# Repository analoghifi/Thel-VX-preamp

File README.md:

### "VX-D" (2007 - 2016):  
* fully discrete circuit (all transistors / no OP-Amps)
* single ended input
* single ended output
* AC coupled input (with film/foil input cap)
* MOSFET Class-A output
* very low-impedance output / is able to drive 1W @ 8Ω (8Ω short-term / 22Ω permanently)
* adjustable gain (16 steps)
* can also be used very well as a "high-end" headphone amplifier
* operating voltage min./max.: ±9V .. ±63V (optimum: ±24V .. ±36V)
  
https://web.archive.org/web/20070809231533/http://www.thel-audioworld.de/module/VXD/vxd.htm  
https://web.archive.org/web/20160325140821/http://thel-audioworld.de/module/VXD/vxd.htm  
<hr>  

### "VX-Line" (from 03/2017):  
* OP-Amp input stage (LME 49720)
* balanced input
* single ended output
* DC coupled
* MOSFET Class-A output (itegrated into the OP-Amps feedback loop)
* very low-impedance output / is able to drive 1W @ 8Ω (8Ω short-term / 22Ω permanently)
* adjustable gain (5 steps)
* can also be used very well as a "high-end" headphone amplifier
* operating voltage min./max.: ±9V .. ±35V (optimum: ±18V .. ±24V)
  
https://web.archive.org/web/20170523101631/http://www.thel-audioworld.de/module/VX-Line/vx-line.htm  
https://web.archive.org/web/20210514101836/http://thel-audioworld.de/module/VX-Line/vx-line.htm  
  
2 different generations of PCB:  
* 2017 - 2020
* from 2021
  
----  
### Kicad projects in this repo:  
* [VX-Line_2021__original](https://github.com/analoghifi/Thel-VX-preamp/tree/main/VX-Line/hardware/KiCad/VX-Line_2021__original) | state: initial release v1.01 | like the original, 1-layer, THT
* [VX-D_original](https://github.com/analoghifi/Thel-VX-preamp/tree/main/VX-D/hardware/KiCad/VX-D_original) | state: coming soon... | like the original, 1-layer, THT

----

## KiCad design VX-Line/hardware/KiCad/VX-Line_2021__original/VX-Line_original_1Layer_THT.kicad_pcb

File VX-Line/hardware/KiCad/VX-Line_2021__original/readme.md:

this is not the original Thel PCB but it's very like\* the original with the following exceptions:  
* more massive ground and power supply PCB tracks  
* using a combined 2.5mm/5.0mm pin spacing footprint for the small ceramic caps (C1,C2,C3,C11)  
  
\*(same schematic / same board dimensions / same 1-layer\** layout THT / same THT components in the same places on the board)  
\**(strictly speaking, this KiCad PCB is a two-layer PCB with plated-through holes, but you can also (let) produce it as a classic 1-layer PCB with non-plated holes if you wish, since all the tracks are on the bottom side only)  

----  

### remarks:  
#### U1:  
instead of [LME49720](https://www2.mouser.com/ProductDetail/Texas-Instruments/LME49720NA-NOPB?qs=7lkVKPoqpbYtIqwyg5iDaA%3D%3D) you can use [LM4562](https://www2.mouser.com/ProductDetail/Texas-Instruments/LM4562NA-NOPB?qs=QbsRYf82W3Gc2w4DLq%252BZjw%3D%3D) (both Texas Instruments),  
these two are 100% identical (even regarding their inner guts).
  
----  

these are KiCad 6.x projects  
see how to get the proper 3D-Models from here: https://github.com/analoghifi/KiCad-3D-Models  

use kicanvas.org to see this KiCad-Project in your browser:  
https://kicanvas.org/?github=https%3A%2F%2Fgithub.com%2Fanaloghifi%2FThel-VX-preamp%2Ftree%2Fmain%2FVX-Line%2Fhardware%2FKiCad%2FVX-Line_2021__original

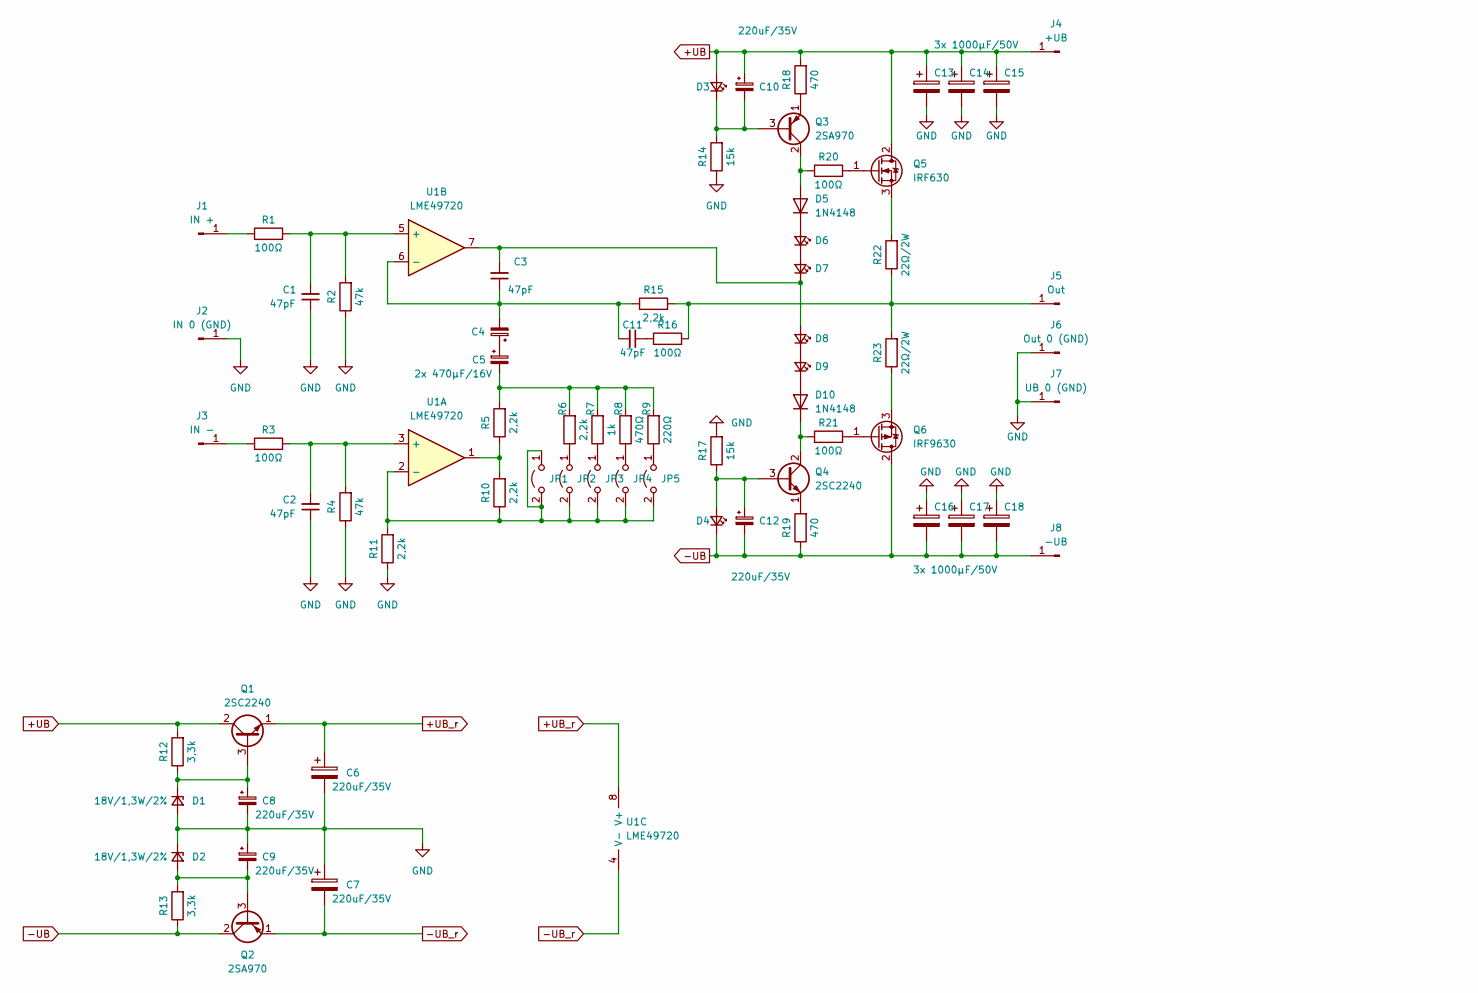
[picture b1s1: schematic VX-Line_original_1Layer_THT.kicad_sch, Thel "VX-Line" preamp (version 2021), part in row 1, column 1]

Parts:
C1, C2, C3, C11: 47pF; C_Rect_L7.0mm_W2.5mm_P2.50_5.00mm_min_silk
C4: 2x 470µF/16V; CP_Radial_Black_D8.2mm_H12.0mm_P3.50mm_minimal_silk
C5: 470µF/16V; CP_Radial_Black_D8.2mm_H12.0mm_P3.50mm_minimal_silk
C6, C7, C8, C9, C10, C12: 220uF/35V; CP_Radial_Black_D8.2mm_H12.0mm_P3.50mm_minimal_silk
C13, C16: 3x 1000µF/50V; CP_Radial_Black_D13.0mm_H26.0mm_P5.00mm_minimal_silk
C14, C15, C17, C18: 1000µF/50V; CP_Radial_Black_D13.0mm_H26.0mm_P5.00mm_minimal_silk
D1, D2: 18V/1,3W/2%; D_DO-41_SOD81_P10.16mm_Horizontal_minSilk
D3, D4: LED_Small; LED_D3.0mm_wide
D5, D10: 1N4148; Diode_L6.3mm_D2.5mm_P10.16mm_Horizontal_minSilk
D6, D7, D8, D9: LED_Small; LED_D3.0mm
J1: IN +; Loet_Pin_D1.5mm_L14.0mm
J2: IN 0 (GND); Loet_Pin_D1.5mm_L14.0mm
J3: IN -; Loet_Pin_D1.5mm_L14.0mm
J4: +UB; Loet_Pin_D1.5mm_L14.0mm
J5: Out; Loet_Pin_D1.5mm_L14.0mm
J6: Out 0 (GND); Loet_Pin_D1.5mm_L14.0mm
J7: UB 0 (GND); Loet_Pin_D1.5mm_L14.0mm
J8: -UB; Loet_Pin_D1.5mm_L14.0mm
JP1, JP2, JP3, JP4, JP5: Jumper_2_Open; PinHeader_1x02_P2.54mm_Vertical
Q1, Q4: 2SC2240; TO-92_wide
Q2, Q3: 2SA970; TO-92_wide
Q5: IRF630; TO-220-3_Vertical
Q6: IRF9630; TO-220-3_Vertical
R1, R3, R20, R21: 100Ω; R_Axial_DIN0207_L6.3mm_D2.5mm_P10.16mm_Horizontal_minSilk
R2, R4: 47k; R_Axial_DIN0207_L6.3mm_D2.5mm_P10.16mm_Horizontal_minSilk
R5, R6, R10, R11: 2,2k; R_Axial_DIN0207_L6.3mm_D2.5mm_P10.16mm_Horizontal_minSilk
R7: 1k; R_Axial_DIN0207_L6.3mm_D2.5mm_P10.16mm_Horizontal_minSilk
R8: 470Ω; R_Axial_DIN0207_L6.3mm_D2.5mm_P10.16mm_Horizontal_minSilk
R9: 220Ω; R_Axial_DIN0207_L6.3mm_D2.5mm_P10.16mm_Horizontal_minSilk
R12, R13: 3,3k; R_Axial_DIN0207_L6.3mm_D2.5mm_P10.16mm_Horizontal_minSilk
R14, R17: 15k; R_Axial_DIN0207_L6.3mm_D2.5mm_P10.16mm_Horizontal_minSilk
R15: 2,2k; R_Axial_Short_L6.3mm_D2.5mm_P9.0mm_Horiz_minSilk
R16: 100Ω; R_Axial_Short_L6.3mm_D2.5mm_P9.0mm_Horiz_minSilk
R18, R19: 470; R_Axial_DIN0207_L6.3mm_D2.5mm_P10.16mm_Horizontal_minSilk
R22, R23: 22Ω/2W; R_Axial_DIN0411_L9.9mm_D3.6mm_P12.70mm_Horizontal
U1: LME49720; DIP-8_W7.62mm

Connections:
+UB: C10.1, C13.1, C14.1, C15.1, D3.2 (A), J4.1, Q1.2 (C), Q5.2 (D), R12.2, R18.2
+UB_r: C6.1, Q1.1 (E), U1.8 (V+)
-UB: C12.2, C16.2, C17.2, C18.2, D4.1 (K), J8.1, Q2.2 (C), Q6.2 (D), R13.1, R19.1
-UB_r: C7.2, Q2.1 (E), U1.4 (V-)
GND: C1.1, C2.1, C6.2, C7.1, C8.2, C9.1, C13.2, C14.2, C15.2, C16.1, C17.1, C18.1, D1.2 (A), D2.1 (K), J2.1, J6.1, J7.1, R2.1, R4.1, R11.1, R14.1, R17.2
unnamed: C1.2, R1.2, R2.2, U1.5 (+)
unnamed: C2.2, R3.2, R4.2, U1.3 (+)
unnamed: C3.2, D7.1 (K), D8.2 (A), U1.7
unnamed: C4.1, C5.1
unnamed: C5.2, R5.2, R6.2, R7.2, R8.2, R9.2
unnamed: C8.1, D1.1 (K), Q1.3 (B), R12.1
unnamed: C9.2, D2.2 (A), Q2.3 (B), R13.2
unnamed: C10.2, D3.1 (K), Q3.3 (B), R14.2
unnamed: C11.1, R16.1
unnamed: C3.1, C4.2, C11.2, R15.1, U1.6 (-)
unnamed: C12.1, D4.2 (A), Q4.3 (B), R17.1
unnamed: D5.1 (K), D6.2 (A)
unnamed: D5.2 (A), Q3.2 (C), R20.1
unnamed: D6.1 (K), D7.2 (A)
unnamed: D8.1 (K), D9.2 (A)
unnamed: D10.1 (K), Q4.2 (C), R21.1
unnamed: D9.1 (K), D10.2 (A)
unnamed: J1.1, R1.1
unnamed: J3.1, R3.1
unnamed: J5.1, R15.2, R16.2, R22.1, R23.2
unnamed: JP1.1 (A), JP1.2 (B), JP2.2 (B), JP3.2 (B), JP4.2 (B), JP5.2 (B), R10.1, R11.2, U1.2 (-)
unnamed: JP2.1 (A), R6.1
unnamed: JP3.1 (A), R7.1
unnamed: JP4.1 (A), R8.1
unnamed: JP5.1 (A), R9.1
unnamed: Q3.1 (E), R18.1
unnamed: Q4.1 (E), R19.2
unnamed: Q5.1 (G), R20.2
unnamed: Q5.3 (S), R22.2
unnamed: Q6.1 (G), R21.2
unnamed: Q6.3 (S), R23.1
unnamed: R5.1, R10.2, U1.1

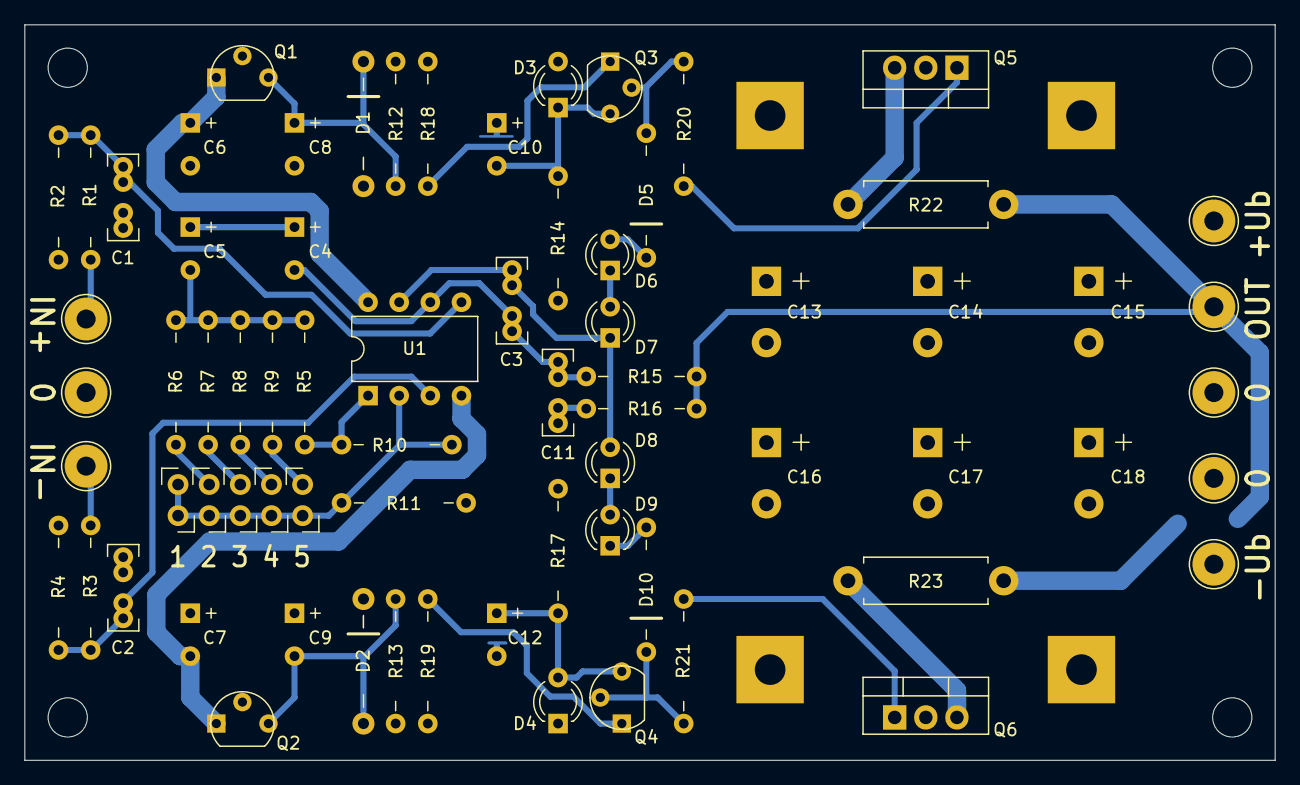
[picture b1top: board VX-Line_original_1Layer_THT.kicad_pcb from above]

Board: 2 copper layers, 102.0 x 60.0 mm, 71 parts (0 on the bottom side), 37 nets.
